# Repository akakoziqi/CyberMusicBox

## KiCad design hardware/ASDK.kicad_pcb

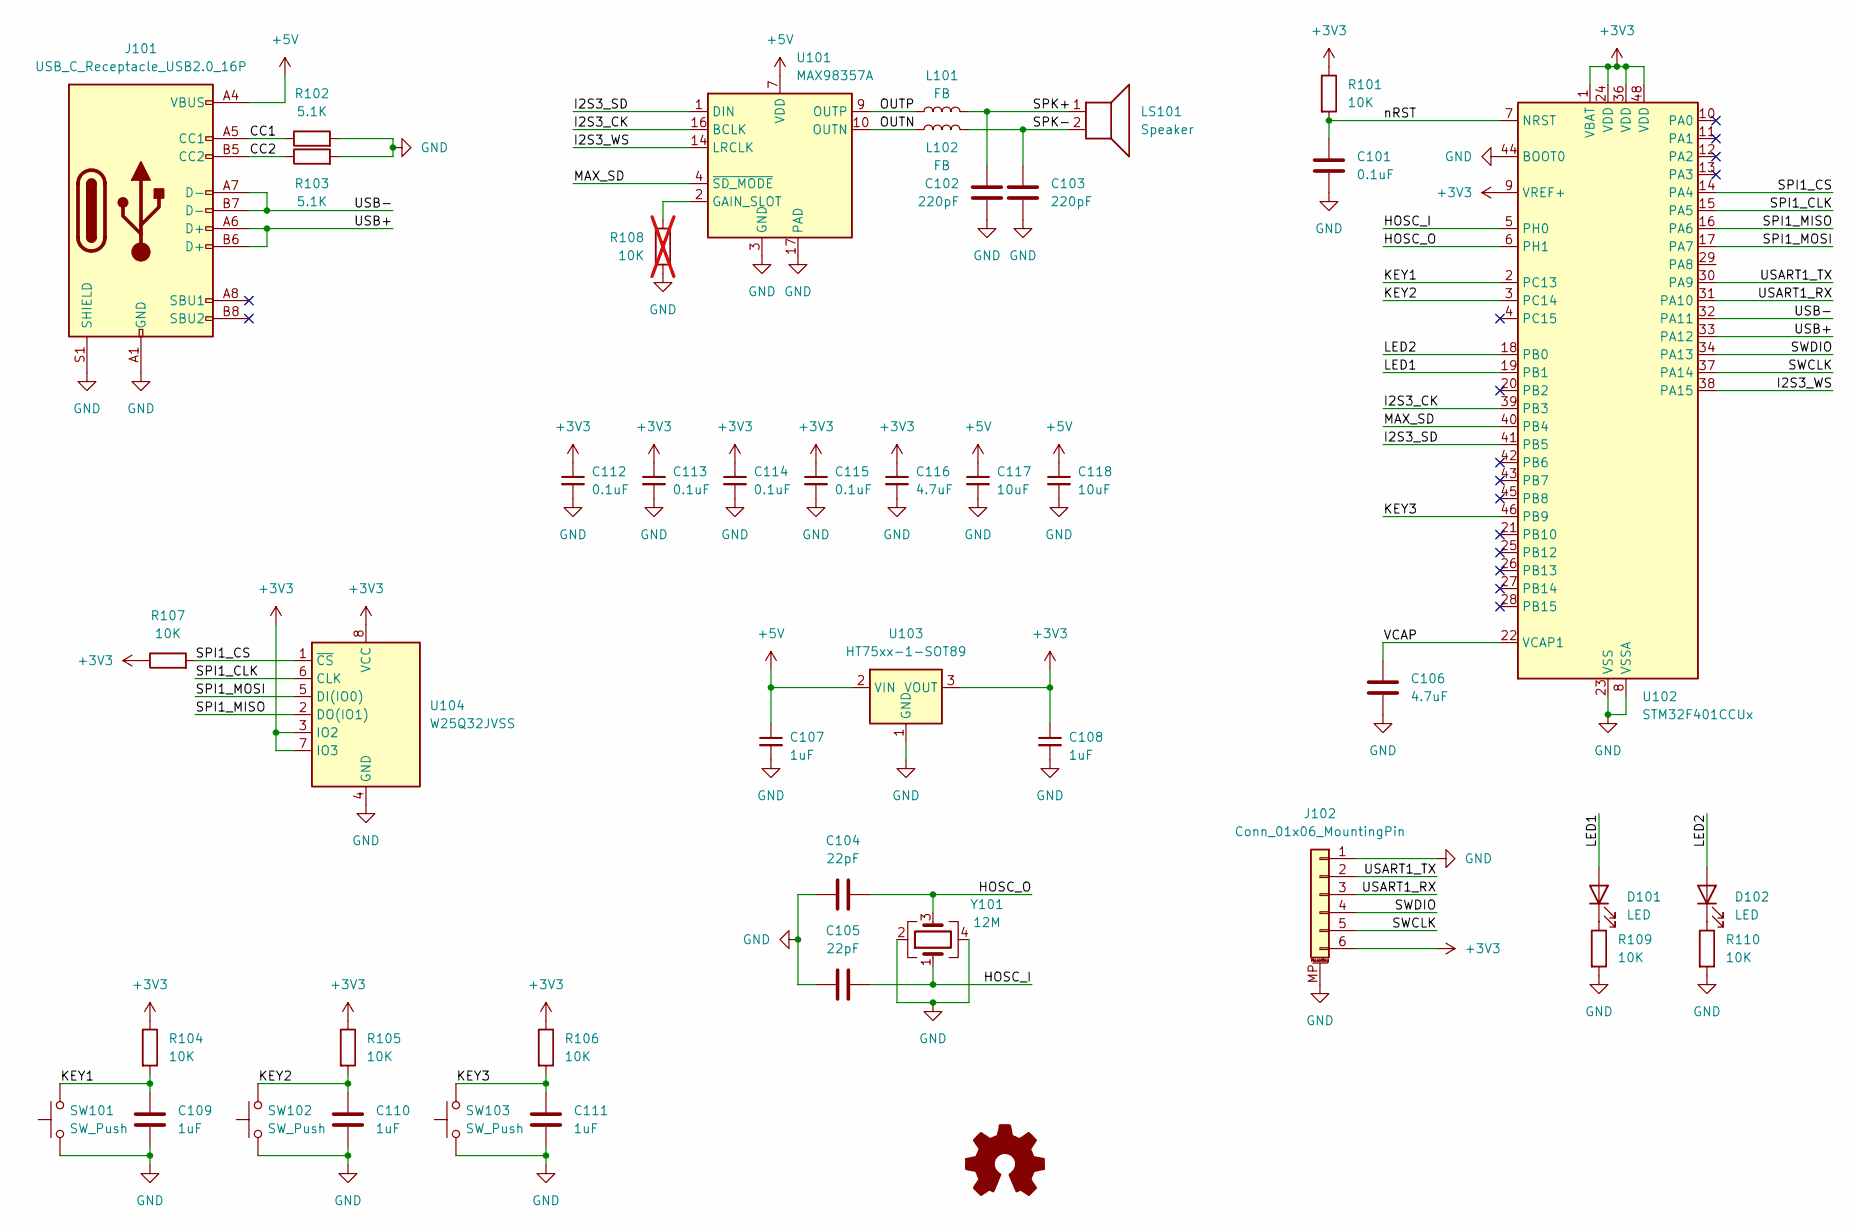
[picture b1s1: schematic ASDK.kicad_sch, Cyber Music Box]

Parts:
C101, C112, C113, C114, C115: 0.1uF; C_0603_1608Metric
C102, C103: 220pF; C_0603_1608Metric
C104, C105: 22pF; C_0603_1608Metric
C106, C116: 4.7uF; C_0603_1608Metric
C107, C108, C109, C110, C111: 1uF; C_0603_1608Metric
C117, C118: 10uF; C_0805_2012Metric
D101, D102: LED; LED_0603_1608Metric
J101: USB_C_Receptacle_USB2.0_16P; USB_C_Receptacle_HRO_TYPE-C-31-M-12
J102: Conn_01x06_MountingPin; JST_GH_SM06B-GHS-TB_1x06-1MP_P1.25mm_Horizontal
L101, L102: FB; L_1206_3216Metric
LS101: Speaker; PinHeader_1x02_P2.54mm_Vertical
R101, R104, R105, R106, R107, R109, R110: 10K; R_0603_1608Metric
R102, R103: 5.1K; R_0603_1608Metric
R108: 10K; R_0603_1608Metric; not fitted
SW101, SW102, SW103: SW_Push; SW_Push_1P1T_NO_CK_KMR2
U101: MAX98357A; TQFN-16-1EP_3x3mm_P0.5mm_EP1.23x1.23mm
U102: STM32F401CCUx; QFN-48-1EP_7x7mm_P0.5mm_EP5.6x5.6mm
U103: HT75xx-1-SOT89; SOT-89-3
U104: W25Q32JVSS; SOIC-8_5.23x5.23mm_P1.27mm
Y101: 12M; Crystal_SMD_3225-4Pin_3.2x2.5mm

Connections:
+3V3: C108.1, C112.1, C113.1, C114.1, C115.1, C116.1, J102.6, R101.1, R104.1, R105.1, R106.1, R107.1, U102.1 (VBAT), U102.9 (VREF+), U102.24 (VDD), U102.36 (VDD), U102.48 (VDD), U103.3 (VOUT), U104.3 (IO2), U104.7 (IO3), U104.8 (VCC)
+5V: C107.1, C117.1, C118.1, J101.A4 (VBUS), J101.A9 (VBUS), J101.B4 (VBUS), J101.B9 (VBUS), U101.7 (VDD), U101.8 (VDD), U103.2 (VIN)
/CC1: J101.A5 (CC1), R102.1
/CC2: J101.B5 (CC2), R103.1
/HOSC_I: C105.2, U102.5 (PH0), Y101.1
/HOSC_O: C104.2, U102.6 (PH1), Y101.3
/I2S3_CK: U101.16 (BCLK), U102.39 (PB3)
/I2S3_SD: U101.1 (DIN), U102.41 (PB5)
/I2S3_WS: U101.14 (LRCLK), U102.38 (PA15)
/KEY1: C109.1, R104.2, SW101.2, U102.2 (PC13)
/KEY2: C110.1, R105.2, SW102.2, U102.3 (PC14)
/KEY3: C111.1, R106.2, SW103.2, U102.46 (PB9)
/LED1: D101.2 (A), U102.19 (PB1)
/LED2: D102.2 (A), U102.18 (PB0)
/MAX_SD: U101.4 (~SD_MODE), U102.40 (PB4)
/OUTN: L102.1, U101.10 (OUTN)
/OUTP: L101.1, U101.9 (OUTP)
/SPI1_CLK: U102.15 (PA5), U104.6 (CLK)
/SPI1_CS: R107.2, U102.14 (PA4), U104.1 (~CS)
/SPI1_MISO: U102.16 (PA6), U104.2 (DO(IO1))
/SPI1_MOSI: U102.17 (PA7), U104.5 (DI(IO0))
/SPK+: C102.1, L101.2, LS101.1
/SPK-: C103.1, L102.2, LS101.2
/SWCLK: J102.5, U102.37 (PA14)
/SWDIO: J102.4, U102.34 (PA13)
/USART1_RX: J102.3, U102.31 (PA10)
/USART1_TX: J102.2, U102.30 (PA9)
/USB+: J101.A6 (D+), J101.B6 (D+), U102.33 (PA12)
/USB-: J101.A7 (D-), J101.B7 (D-), U102.32 (PA11)
/VCAP: C106.1, U102.22 (VCAP1)
/nRST: C101.1, R101.2, U102.7 (NRST)
GND: C101.2, C102.2, C103.2, C104.1, C105.1, C106.2, C107.2, C108.2, C109.2, C110.2, C111.2, C112.2, C113.2, C114.2, C115.2, C116.2, C117.2, C118.2, J101.A1 (GND), J101.A12 (GND), J101.B1 (GND), J101.B12 (GND), J101.S1 (SHIELD), J102.1, J102.MP (MountPin), R102.2, R103.2, R108.2, R109.2, R110.2, SW101.1, SW102.1, SW103.1, U101.3 (GND), U101.11 (GND), U101.15 (GND), U101.17 (PAD), U102.8 (VSSA), U102.23 (VSS), U102.35 (VSS), U102.44 (BOOT0), U102.47 (VSS), U102.49 (VSS), U103.1 (GND), U104.4 (GND), Y101.2, Y101.4
unnamed: D101.1 (K), R109.1
unnamed: D102.1 (K), R110.1
unnamed: R108.1, U101.2 (GAIN_SLOT)

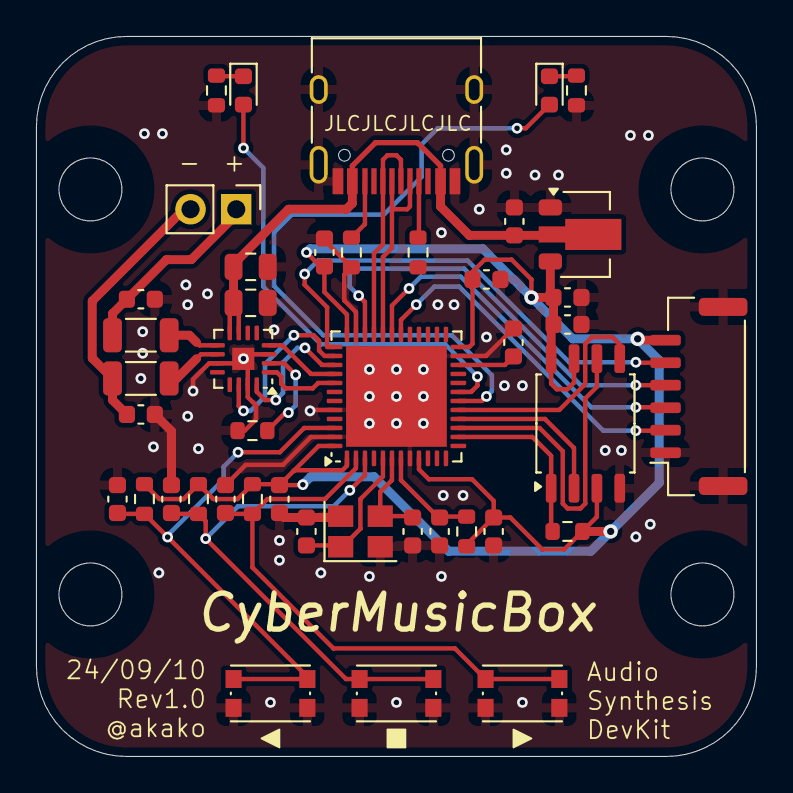
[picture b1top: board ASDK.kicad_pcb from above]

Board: 2 copper layers, 40.0 x 40.0 mm, 43 parts (0 on the bottom side), 35 nets.

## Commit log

2024-09-10 [add] hardware project
